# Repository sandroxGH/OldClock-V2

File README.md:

Old Clock V2.0
===================== 
Controller board for Odl train station clock 

Project preview
=====================

License and copyright
=====================

Copyright 2017-2018 sandroxGH infomsystemsrl@gmail.com

Licensed under the Apache License, Version 2.0 (the "License"); you may not use this file except in compliance with the License. You may obtain a copy of the License at http://www.apache.org/licenses/LICENSE-2.0

Unless required by applicable law or agreed to in writing, software distributed under the License is distributed on an "AS IS" BASIS, WITHOUT WARRANTIES OR CONDITIONS OF ANY KIND, either express or implied. See the License for the specific language governing permissions and limitations under the License.

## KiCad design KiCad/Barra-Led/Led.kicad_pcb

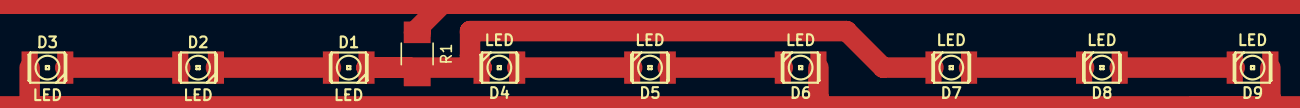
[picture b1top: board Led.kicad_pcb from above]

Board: 2 copper layers, 10 parts (0 on the bottom side), 8 nets.

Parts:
D1, D2, D3, D4, D5, D6, D7, D8, D9: LED; 3528
R1: R; R_1210_HandSoldering

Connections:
unnamed: D1.1, D2.2
unnamed: D1.2, D4.2, D7.2, R1.2
unnamed: D2.1, D3.2
unnamed: D3.1, D6.1, D9.1
unnamed: D4.1, D5.2
unnamed: D5.1, D6.2
unnamed: D7.1, D8.2
unnamed: D8.1, D9.2

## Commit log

2017-12-11 New Repo
2018-02-07 Updated schematics
2018-02-07 Added documentation for eeprom rear/write rouitne
2018-02-07 EEprom24C32 library
2018-02-07 Added datasheet
2018-02-07 Modified file
2018-02-07 Event/Alarm log procedure. Eeprom wipe read procedure. Eeprom read/write procedure enhanced. Comment translations
2018-02-08 added pictures and modified readme
2018-02-08 Picture update
2018-02-28 Modified Enable and Dir pin to avoid motor revolution during the USB reset Addere a restart procedure if the 12V go down for a small period
2018-02-28 Modified SCH Enable and Dir pin to avoid motor revolution during the USB reset
2018-02-28 Step Down regulator Q
2018-02-28 Rename KiCad Project and pdf file
2018-03-01 New PCB for led light ba
2018-03-03 Bug fix on Twilight On Off Setting, Modified autoreset procedure
2018-03-04 Bug fix on Event Allrm Log A5 A6
2018-03-04 Documentation for Upgarde
2018-03-06 Removed Doc Folder
2018-03-07 Work on code indentation and comments. Added mechanical time in menu page to edit the time. Added a waiting procedure with mechanical clock in advance of 60 min
2020-05-28 Schematical update
2020-05-28 Millis overflow prevent
    Modified all the timer logic
2020-05-29 Test with DS3231
    Same CTR address modified EEPROM address from 0x50>0x57
2020-06-01 Update for DS3231
    Schematical and library update
    New eeprom address.
    chmage pinout from simulator to final board
2020-06-04 Auto Adjust summer time standard time
2020-06-05 Add event for summer standard time adj
    Event 12 summer time
    event 13 standard time
2023-07-01 KiCad file update
2023-07-01 Schematical and code update Schematical resistor valude in Vsens code to comment the Vsens Ratio
